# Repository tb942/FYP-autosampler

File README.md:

# Thomas Butler's University of Liverpool Final Year Project
## Autosampler
 This repository holds the design files and source code for Thomas Butler's UOL Final Year Project.

### Arduino firmware
The firmware for this project is [Autosampler_firmware.ino](Arduino/Autosampler_firmware/Autosampler_firmware.ino).
To install, place the contents of the [Arduino](Arduino) folder in your Arduino IDE's sketchbook location.

### GUI software
The source files for the Qt creator project are in the [GUI](GUI) folder.

### CAD files
You can get the Fusion 360 assembly file [here](https://a360.co/32DXsge).

### PCB files
The Eagle CAD files and Gerber outputs for the main PCB can be found in the [PCB](PCB) folder.

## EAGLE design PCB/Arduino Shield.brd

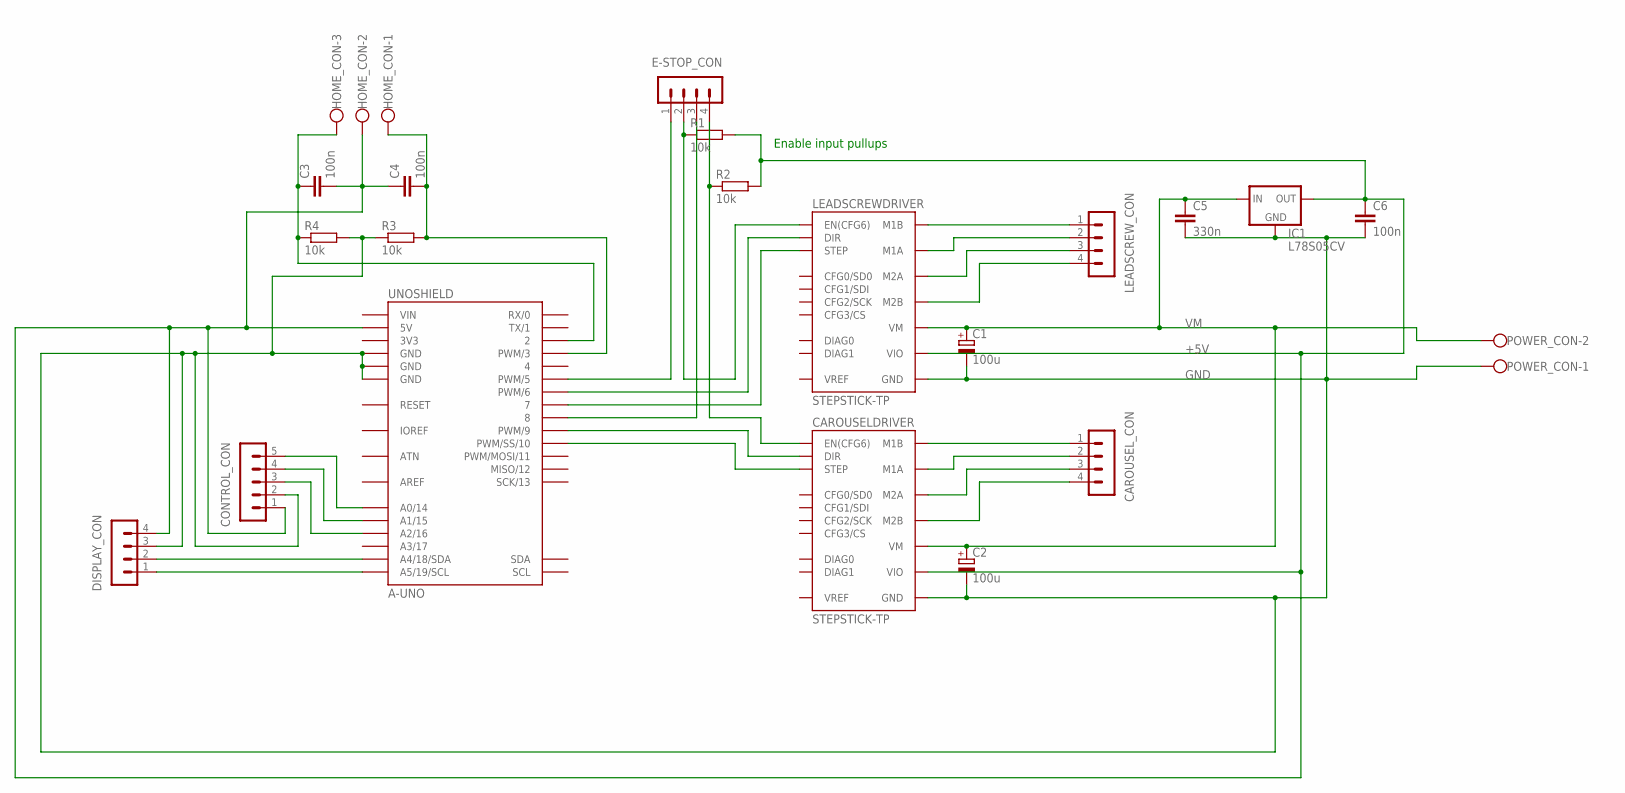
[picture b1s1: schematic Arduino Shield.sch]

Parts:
C1, C2: 100u; E3,5-8
C3, C4: 100n; C025-024X044
C5: 330n; C025-030X050
C6: 100n; C025-030X050
CAROUSELDRIVER: STEPSTICK-TP; STEPSTICK_TP
CAROUSEL_CON: MA04-1
CONTROL_CON: MA05-1
DISPLAY_CON: MA04-1
E-STOP_CON: MA04-1
HOME_CON: W237-103
IC1: L78S05CV; TO-220-STANDING
LEADSCREWDRIVER: STEPSTICK-TP; STEPSTICK_TP
LEADSCREW_CON: MA04-1
POWER_CON: W237-102
R1, R2: 10k; 0207/12
R3, R4: 10k; 0207/10
UNOSHIELD: A-UNO

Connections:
3V3: UNOSHIELD.3V3
+5V: C3.2, C4.1, C6.1, CAROUSELDRIVER.VIO, CONTROL_CON.1, DISPLAY_CON.4, HOME_CON.2, IC1.3 (OUT), LEADSCREWDRIVER.VIO, R1.2, R2.2, UNOSHIELD.5V
AREF: UNOSHIELD.AREF
GND: C1.-, C2.-, C5.2, C6.2, CAROUSELDRIVER.GND@1 (GND), CAROUSELDRIVER.GND@2 (GND), CONTROL_CON.2, DISPLAY_CON.3, IC1.2 (GND), LEADSCREWDRIVER.GND@1 (GND), LEADSCREWDRIVER.GND@2 (GND), POWER_CON.1, R3.1, R4.2, UNOSHIELD.GND@1 (GND), UNOSHIELD.GND@2 (GND), UNOSHIELD.GND@3 (GND)
IOREF: UNOSHIELD.IOREF
unnamed: E-STOP_CON.2, LEADSCREWDRIVER.EN (EN(CFG6)), R1.1
unnamed: LEADSCREWDRIVER.DIR, UNOSHIELD.6 (PWM/6)
unnamed: LEADSCREWDRIVER.STEP, UNOSHIELD.7
unnamed: CAROUSELDRIVER.EN (EN(CFG6)), E-STOP_CON.4, R2.1
unnamed: CAROUSELDRIVER.DIR, UNOSHIELD.9 (PWM/9)
unnamed: CAROUSELDRIVER.STEP, UNOSHIELD.10 (PWM/SS/10)
unnamed: LEADSCREWDRIVER.M1B, LEADSCREW_CON.1
unnamed: LEADSCREWDRIVER.M1A, LEADSCREW_CON.2
unnamed: LEADSCREWDRIVER.M2B, LEADSCREW_CON.4
unnamed: LEADSCREWDRIVER.M2A, LEADSCREW_CON.3
unnamed: CAROUSELDRIVER.M1B, CAROUSEL_CON.1
unnamed: CAROUSELDRIVER.M1A, CAROUSEL_CON.2
unnamed: CAROUSELDRIVER.M2A, CAROUSEL_CON.3
unnamed: CAROUSELDRIVER.M2B, CAROUSEL_CON.4
unnamed: E-STOP_CON.1, UNOSHIELD.5 (PWM/5)
unnamed: E-STOP_CON.3, UNOSHIELD.8
unnamed: DISPLAY_CON.1, UNOSHIELD.A5 (A5/19/SCL)
unnamed: DISPLAY_CON.2, UNOSHIELD.A4 (A4/18/SDA)
unnamed: C3.1, HOME_CON.3, R4.1, UNOSHIELD.2
unnamed: CONTROL_CON.5, UNOSHIELD.A0 (A0/14)
unnamed: CONTROL_CON.4, UNOSHIELD.A1 (A1/15)
unnamed: CONTROL_CON.3, UNOSHIELD.A2 (A2/16)
unnamed: C4.2, HOME_CON.1, R3.2, UNOSHIELD.3 (PWM/3)
VIN: UNOSHIELD.VIN
VM: C1.+, C2.+, C5.1, CAROUSELDRIVER.VM, IC1.1 (IN), LEADSCREWDRIVER.VM, POWER_CON.2

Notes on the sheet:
Enable input pullups

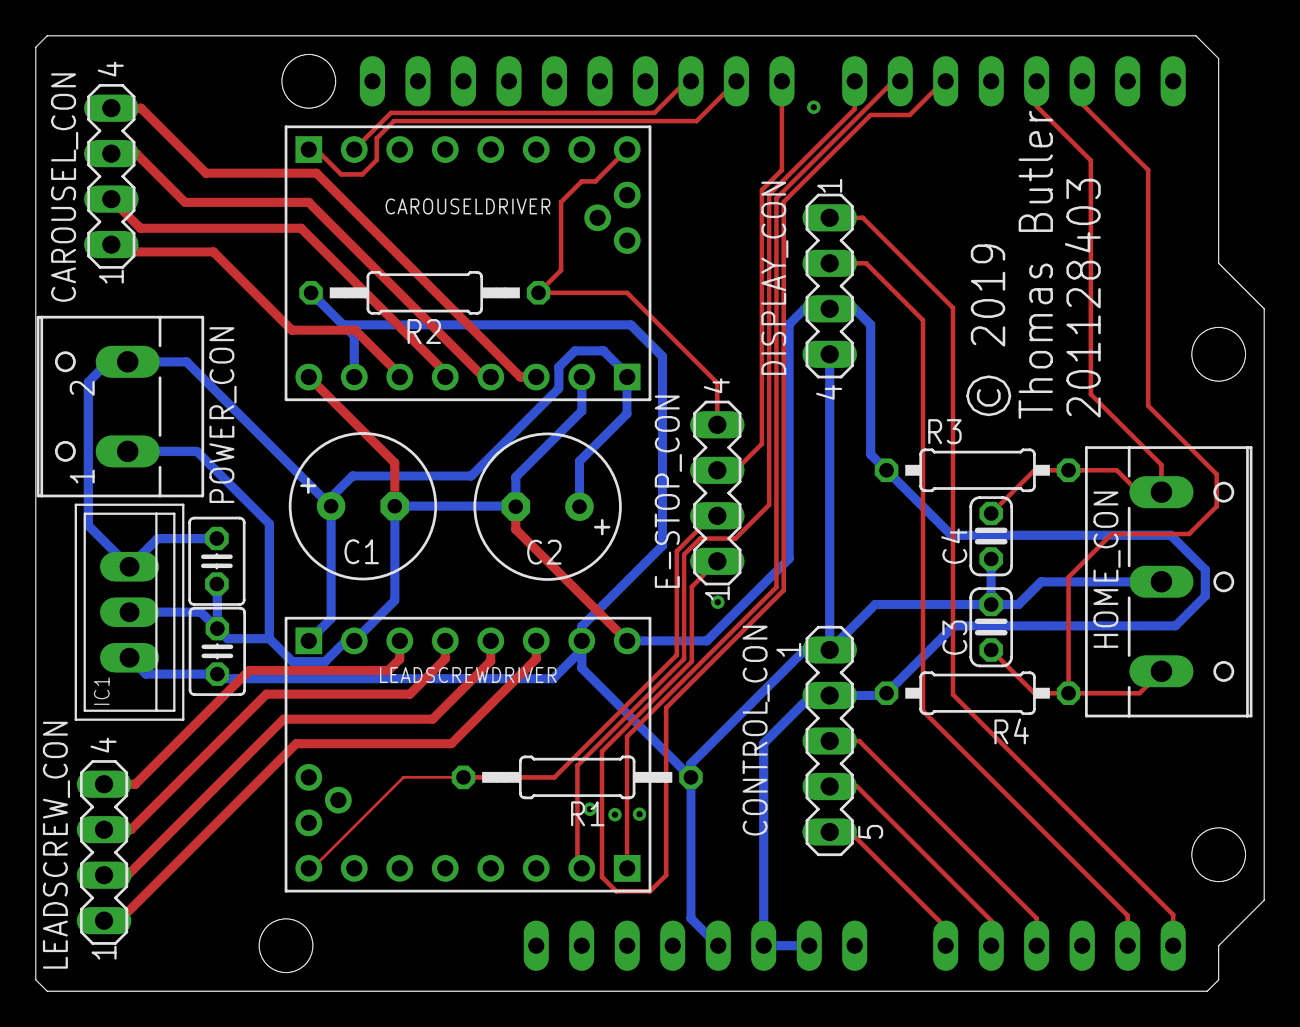
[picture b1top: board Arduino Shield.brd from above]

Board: 2 copper layers, 68.6 x 53.3 mm, 21 parts (0 on the bottom side), 26 nets.

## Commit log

2020-04-11 Added files
2020-04-11 Type corrections
2020-04-11 Removed excess files
2020-04-11 Removed redundant capacitive sensor library
2020-04-11 Removed unnecesary qualification
2020-04-11 Made const static - it should be
2020-04-21 Re-structured
2020-04-21 Included GUI and updated readme
2020-04-21 Added images
2020-04-21 Added PCB files
2020-04-22 Added more resources

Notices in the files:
PCB/Arduino Shield.brd:
© 2019
